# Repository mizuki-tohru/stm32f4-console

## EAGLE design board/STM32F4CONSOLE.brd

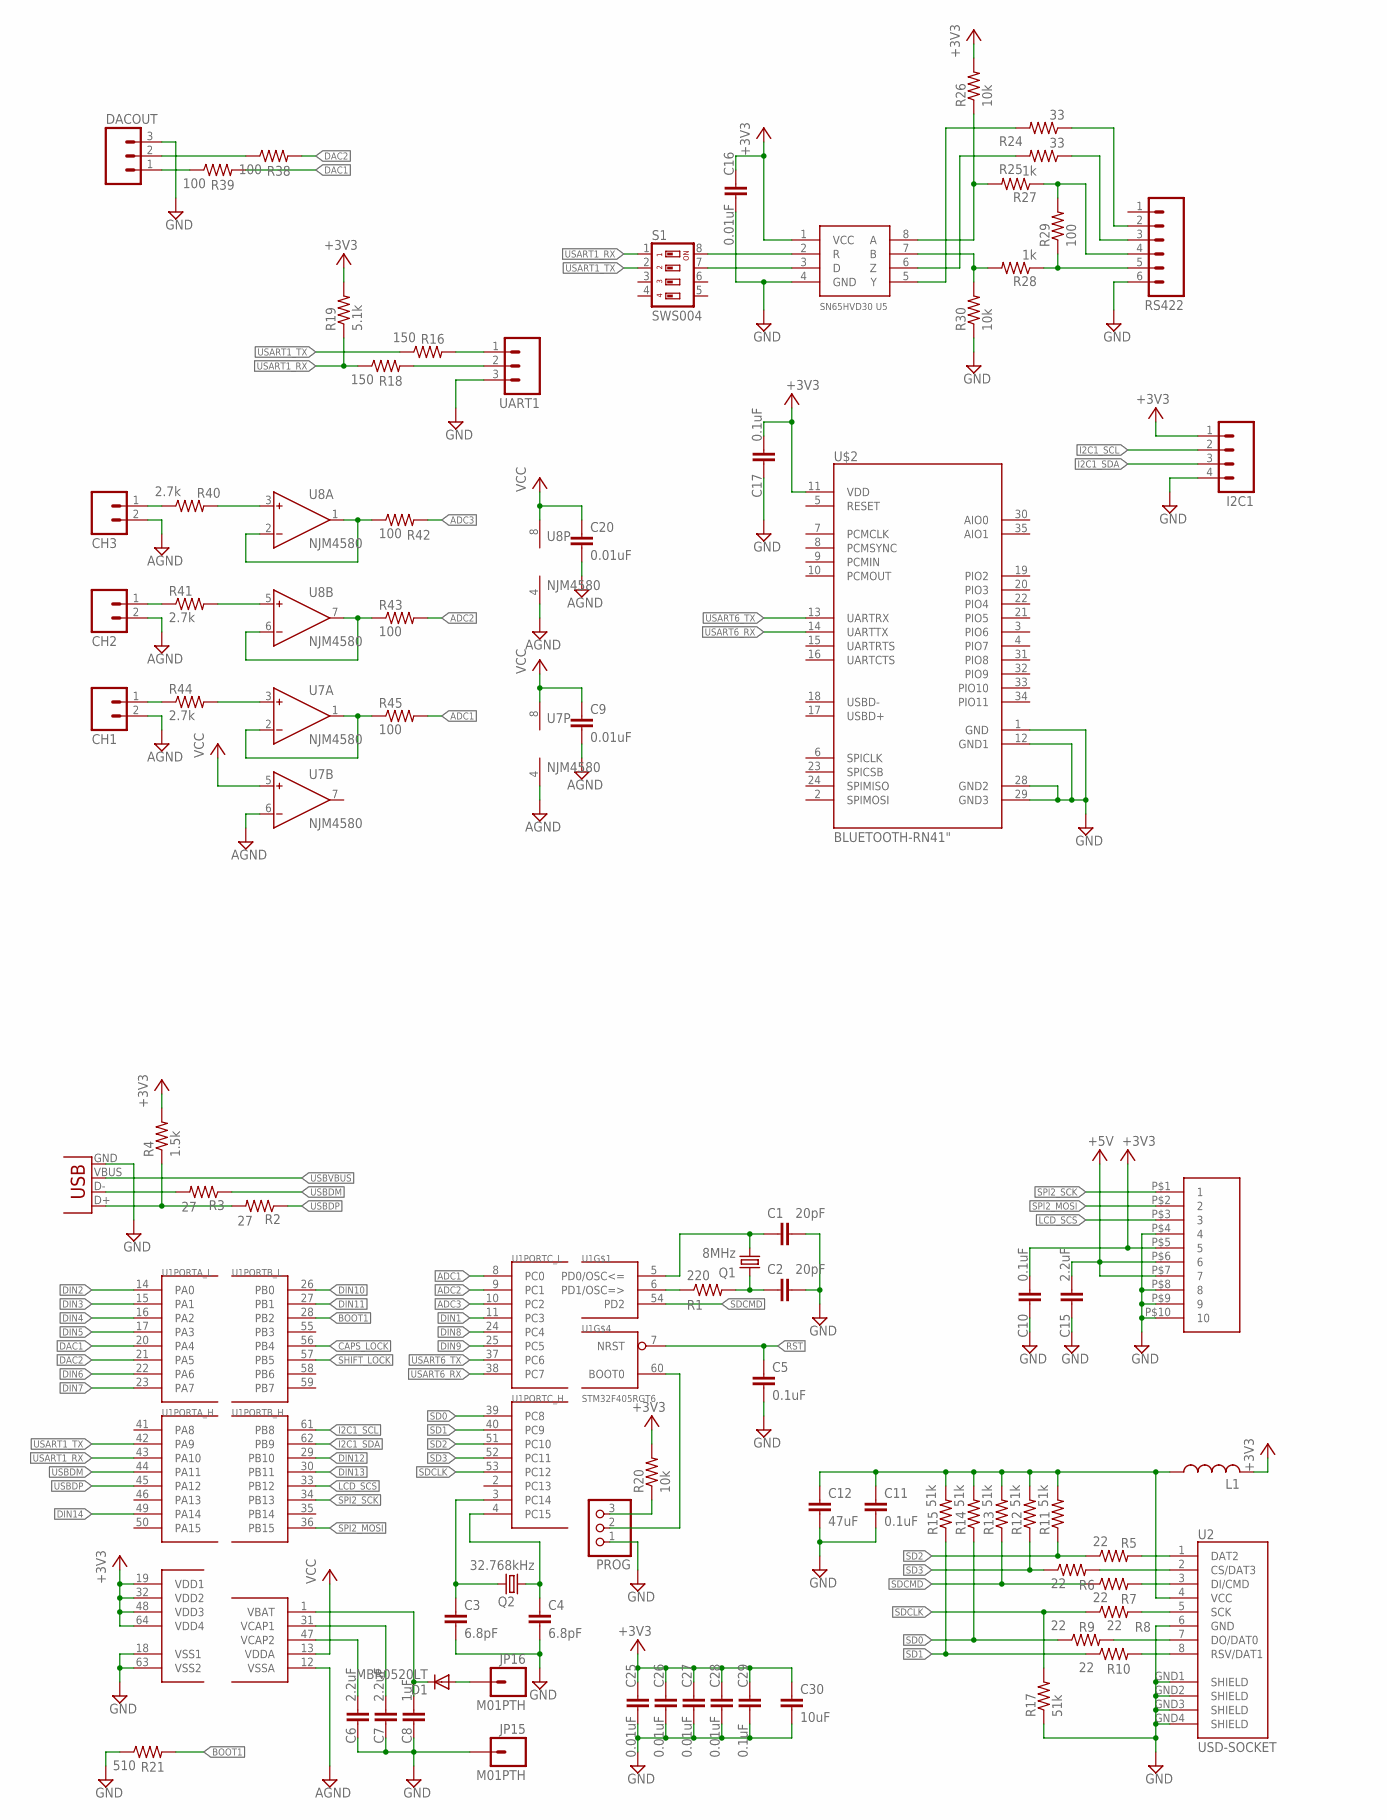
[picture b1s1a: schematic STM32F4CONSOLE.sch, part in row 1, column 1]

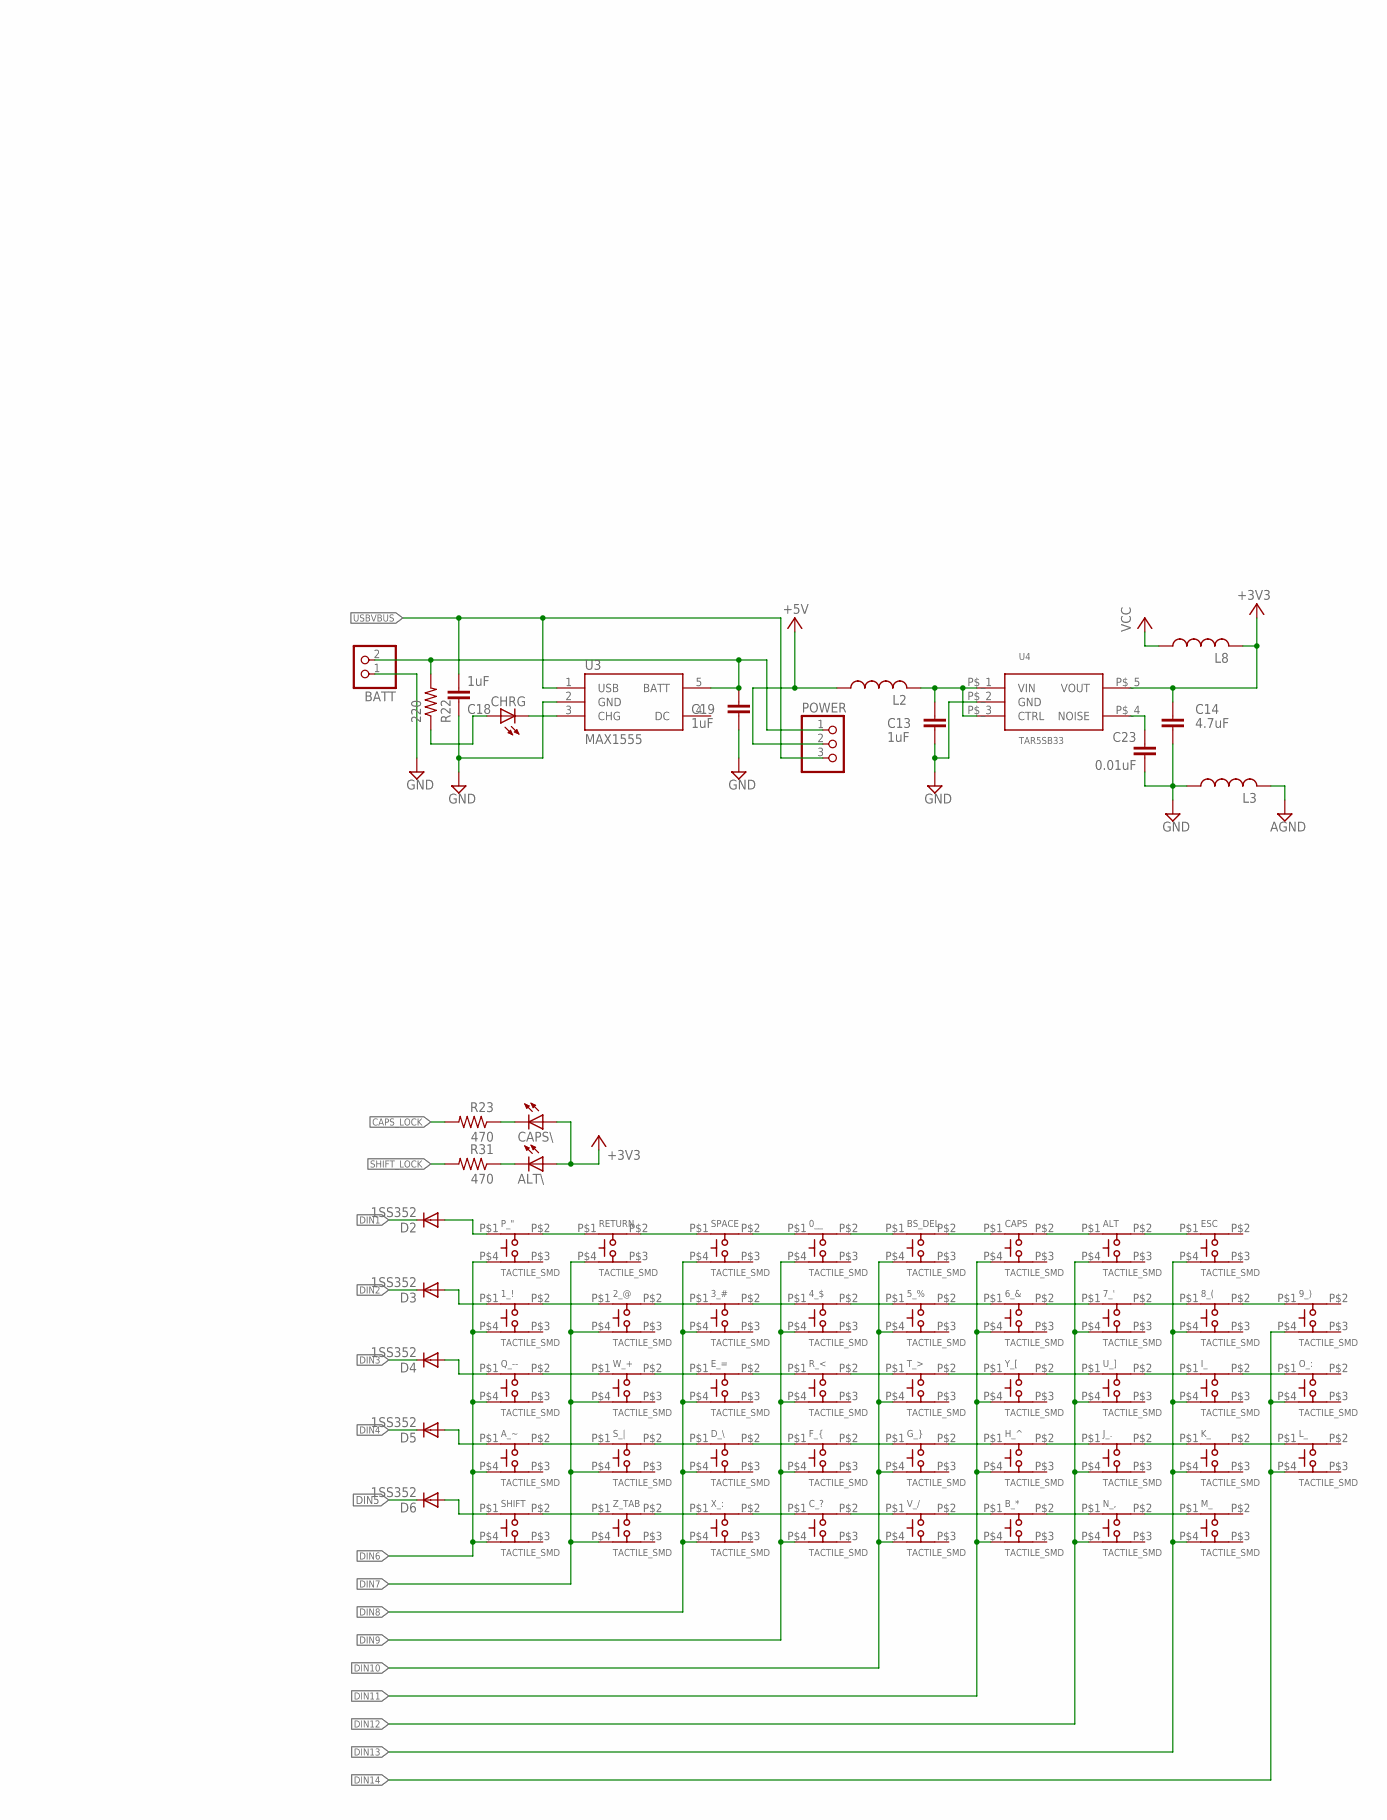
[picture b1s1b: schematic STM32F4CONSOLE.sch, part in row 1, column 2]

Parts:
0__, 1_!, 2_@, 3_#, 4_$, 5_%, 6_&, 7_', 8_(, 9_): TACTILE_SMD
ALT: TACTILE_SMD
ALT\: LED0603; LED-0603
A_~: TACTILE_SMD
BATT: PINHD-1X2; 1X02
BS_DEL: TACTILE_SMD
B_*: TACTILE_SMD
C1, C2: 20pF; C0603
C3, C4: 6.8pF; C0603
C5, C10, C11, C17, C29: 0.1uF; C0603
C6, C7, C15: 2.2uF; C0805
C8: 1uF; C1608
C9, C16, C20, C23, C25, C26, C27, C28: 0.01uF; C0603
C12: 47uF; C3225
C13, C18, C19: 1uF; C2012
C14: 4.7uF; C2012
C30: 10uF; C3216
CAPS: TACTILE_SMD
CAPS\: LED0603; LED-0603
CH1, CH2, CH3: M02PTH; 1X02
CHRG: LED0603; LED-0603
C_?: TACTILE_SMD
D1: MBR0520LT; SOD123
D2, D3, D4, D5, D6: 1SS352; SOD-323
DACOUT: M03PTH; 1X03
D_\\: TACTILE_SMD
ESC: TACTILE_SMD
E_=: TACTILE_SMD
F_{: TACTILE_SMD
G_}: TACTILE_SMD
H_^: TACTILE_SMD
I2C1: M04PTH; 1X04
I_: TACTILE_SMD
JP15, JP16: M01PTH; 1X01
J_.: TACTILE_SMD
K_: TACTILE_SMD
L1, L2, L3, L8: L-USL3216C; L3216C
L_: TACTILE_SMD
M_: TACTILE_SMD
N_,: TACTILE_SMD
O_:: TACTILE_SMD
POWER: PINHD-1X3; 1X03
PROG: PINHD-1X3; 1X03
P_": TACTILE_SMD
Q1: 8MHz; HC49/S
Q2: 32.768kHz; TC26H
Q_--: TACTILE_SMD
R1, R22: 220; R0603
R2, R3: 27; R0603
R4: 1.5k; R0603
R5, R6, R7, R8, R9, R10: 22; R0603
R11, R12, R13, R14, R15, R17: 51k; R0603
R16, R18: 150; R0603
R19: 5.1k; R0603
R20, R26, R30: 10k; R0603
R21: 510; R0603
R23, R31: 470; R0603
R24, R25: 33; R0603
R27, R28: 1k; R0603
R29, R38, R39, R42, R43, R45: 100; R0603
R40, R41, R44: 2.7k; R0805
RETURN: TACTILE_SMD
RS422: M06SIP; 1X06
R_<: TACTILE_SMD
S1: SWS004; SMSS-004
SHIFT: TACTILE_SMD
SPACE: TACTILE_SMD
S_|: TACTILE_SMD
T_>: TACTILE_SMD
U1: STM32F405RGT6; TQFP64
U2: USD-SOCKET; MICRO-SD-SOCKET-PP
U3: MAX1555; SOT23-5
U4: TAR5SB33
U5: SN65HVD30; SO8
U6: FH12-10S-05; FH12-10S-0.5SH
U7, U8: NJM4580; SO08
U$2: BLUETOOTH-RN41"; RN41
UART1: M03PTH; 1X03
U_]: TACTILE_SMD
V_/: TACTILE_SMD
W_+: TACTILE_SMD
X1: USBOLD; USB-MINIB-OLD
X_:: TACTILE_SMD
Y_[: TACTILE_SMD
Z_TAB: TACTILE_SMD

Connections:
+3V3: ALT\.A, C10.1, C14.1, C16.1, C17.1, C25.1, C26.1, C27.1, C28.1, C29.1, C30.1, CAPS\.A, I2C1.1, L1.2, L8.2, R4.2, R19.2, R20.2, R26.2, U1.19 (VDD1), U1.32 (VDD2), U1.48 (VDD3), U1.64 (VDD4), U4.P$_5 (VOUT), U5.1 (VCC), U6.P$5 (5), U$2.11 (VDD)
+5V: C15.1, L2.1, POWER.2, U6.P$6 (6), U6.P$7 (7)
ADC1: R45.2, U1.8 (PC0)
ADC2: R43.2, U1.9 (PC1)
ADC3: R42.2, U1.10 (PC2)
AGND: C9.2, C20.2, CH1.2, CH2.2, CH3.2, L3.2, U1.12 (VSSA), U7.4 (V-), U7.6 (IN-), U8.4 (V-)
BOOT1: R21.2, U1.28 (PB2)
CAPS_LOCK: R23.2, U1.56 (PB4)
DAC1: R39.2, U1.20 (PA4)
DAC2: R38.2, U1.21 (PA5)
DIN1: D2.1 (C), U1.11 (PC3)
DIN2: D3.1 (C), U1.14 (PA0)
DIN3: D4.1 (C), U1.15 (PA1)
DIN4: D5.1 (C), U1.16 (PA2)
DIN5: D6.1 (C), U1.17 (PA3)
DIN6: 1_!.P$4, A_~.P$4, P_".P$4, Q_--.P$4, SHIFT.P$4, U1.22 (PA6)
DIN7: 2_@.P$4, RETURN.P$4, S_|.P$4, U1.23 (PA7), W_+.P$4, Z_TAB.P$4
DIN8: 3_#.P$4, D_\\.P$4, E_=.P$4, SPACE.P$4, U1.24 (PC4), X_:.P$4
DIN9: 0__.P$4, 4_$.P$4, C_?.P$4, F_{.P$4, R_<.P$4, U1.25 (PC5)
DIN10: 5_%.P$4, BS_DEL.P$4, G_}.P$4, T_>.P$4, U1.26 (PB0), V_/.P$4
DIN11: 6_&.P$4, B_*.P$4, CAPS.P$4, H_^.P$4, U1.27 (PB1), Y_[.P$4
DIN12: 7_'.P$4, ALT.P$4, J_..P$4, N_,.P$4, U1.29 (PB10), U_].P$4
DIN13: 8_(.P$4, ESC.P$4, I_.P$4, K_.P$4, M_.P$4, U1.30 (PB11)
DIN14: 9_).P$4, L_.P$4, O_:.P$4, U1.49 (PA14)
DIN_2: 6_&.P$2, 7_'.P$1
DIN_3: I_.P$2, O_:.P$1
DIN_4: J_..P$2, K_.P$1
DIN_5: B_*.P$2, N_,.P$1
GND: BATT.1, C1.2, C2.2, C3.2, C4.2, C5.2, C6.2, C7.2, C8.2, C10.2, C11.2, C12.2, C13.2, C14.2, C15.2, C16.2, C17.2, C18.2, C19.2, C23.2, C25.2, C26.2, C27.2, C28.2, C29.2, C30.2, DACOUT.3, I2C1.4, JP15.1, L3.1, PROG.1, R17.1, R21.1, R30.1, RS422.6, U1.18 (VSS1), U1.63 (VSS2), U2.6 (GND), U2.GND1 (SHIELD), U2.GND2 (SHIELD), U2.GND3 (SHIELD), U2.GND4 (SHIELD), U3.2 (GND), U4.P$_2 (GND), U5.4 (GND), U6.P$4 (4), U6.P$8 (8), U6.P$9 (9), U6.P$10 (10), U$2.1 (GND), U$2.12 (GND1), U$2.28 (GND2), U$2.29 (GND3), UART1.3, X1.GND
I2C1_SCL: I2C1.2, U1.61 (PB8)
I2C1_SDA: I2C1.3, U1.62 (PB9)
LCD_SCS: U1.33 (PB12), U6.P$3 (3)
unnamed: R1.1, U1.6 (PD1/OSC=>)
unnamed: C2.1, Q1.1, R1.2
unnamed: C1.1, Q1.2, U1.5 (PD0/OSC<=)
unnamed: C6.1, U1.47 (VCAP2)
unnamed: C7.1, U1.31 (VCAP1)
unnamed: C4.1, Q2.2, U1.4 (PC15)
unnamed: C3.1, Q2.1, U1.3 (PC14)
unnamed: C8.1, D1.C, U1.1 (VBAT)
unnamed: R5.2, U2.1 (DAT2)
unnamed: R6.2, U2.2 (CS/DAT3)
unnamed: R7.2, U2.3 (DI/CMD)
unnamed: D1.A, JP16.1
unnamed: R8.2, U2.5 (SCK)
unnamed: R9.2, U2.7 (DO/DAT0)
unnamed: R10.2, U2.8 (RSV/DAT1)
unnamed: BATT.2, C19.1, POWER.1, R22.2, U3.5 (BATT)
unnamed: R3.2, X1.D-
unnamed: R2.2, R4.1, X1.D+
unnamed: R18.2, UART1.2
unnamed: R16.2, UART1.1
unnamed: PROG.2, U1.60 (BOOT0)
unnamed: C13.1, L2.2, U4.P$_1 (VIN), U4.P$_3 (CTRL)
unnamed: CHRG.A, R22.1
unnamed: CHRG.C, U3.3 (CHG)
unnamed: D2.2 (A), P_".P$1
unnamed: P_".P$2, RETURN.P$1
unnamed: RETURN.P$2, SPACE.P$1
unnamed: 0__.P$1, SPACE.P$2
unnamed: C11.1, C12.1, L1.1, R11.2, R12.2, R13.2, R14.2, R15.2, U2.4 (VCC)
unnamed: 0__.P$2, BS_DEL.P$1
unnamed: 1_!.P$1, D3.2 (A)
unnamed: 1_!.P$2, 2_@.P$1
unnamed: D6.2 (A), SHIFT.P$1
unnamed: SHIFT.P$2, Z_TAB.P$1
unnamed: C23.1, U4.P$_4 (NOISE)
unnamed: X_:.P$1, Z_TAB.P$2
unnamed: C_?.P$1, X_:.P$2
unnamed: C_?.P$2, V_/.P$1
unnamed: A_~.P$2, S_|.P$1
unnamed: F_{.P$2, G_}.P$1
unnamed: CH3.1, R40.1
unnamed: DACOUT.1, R39.1
unnamed: DACOUT.2, R38.1
unnamed: R40.2, U8.3 (IN+)
unnamed: CH2.1, R41.1
unnamed: R41.2, U8.5 (IN+)
unnamed: R43.1, U8.6 (IN-), U8.7 (OUT)
unnamed: R42.1, U8.1 (OUT), U8.2 (IN-)
unnamed: CH1.1, R44.1
unnamed: R44.2, U7.3 (IN+)
unnamed: R45.1, U7.1 (OUT), U7.2 (IN-)
unnamed: PROG.3, R20.1
unnamed: D_\\.P$2, F_{.P$1
unnamed: D_\\.P$1, S_|.P$2
unnamed: A_~.P$1, D5.2 (A)
unnamed: D4.2 (A), Q_--.P$1
unnamed: Q_--.P$2, W_+.P$1
unnamed: E_=.P$1, W_+.P$2
unnamed: E_=.P$2, R_<.P$1
unnamed: R_<.P$2, T_>.P$1
unnamed: 2_@.P$2, 3_#.P$1
unnamed: 3_#.P$2, 4_$.P$1
unnamed: 4_$.P$2, 5_%.P$1
unnamed: BS_DEL.P$2, CAPS.P$1
unnamed: ALT.P$1, CAPS.P$2
unnamed: ALT.P$2, ESC.P$1
unnamed: S1.7, U5.3 (D)
unnamed: S1.8, U5.2 (R)
unnamed: R24.2, U5.5 (Y)
unnamed: 8_(.P$2, 9_).P$1
unnamed: 7_'.P$2, 8_(.P$1
unnamed: 5_%.P$2, 6_&.P$1
unnamed: T_>.P$2, Y_[.P$1
unnamed: U_].P$1, Y_[.P$2
unnamed: I_.P$1, U_].P$2
unnamed: K_.P$2, L_.P$1
unnamed: R25.2, U5.6 (Z)
unnamed: M_.P$1, N_,.P$2
unnamed: B_*.P$1, V_/.P$2
unnamed: G_}.P$2, H_^.P$1
unnamed: H_^.P$2, J_..P$1
unnamed: R28.2, R30.2, U5.7 (B)
unnamed: R26.1, R27.2, U5.8 (A)
unnamed: R28.1, R29.1, RS422.5
unnamed: R27.1, R29.2, RS422.4
unnamed: R25.1, RS422.3
unnamed: R24.1, RS422.2
unnamed: CAPS\.C, R23.1
unnamed: ALT\.C, R31.1
RST: C5.1, U1.7 (NRST)
SD0: R9.1, R14.1, U1.39 (PC8)
SD1: R10.1, R15.1, U1.40 (PC9)
SD2: R5.1, R11.1, U1.51 (PC10)
SD3: R6.1, R12.1, U1.52 (PC11)
SDCLK: R8.1, R17.2, U1.53 (PC12)
SDCMD: R7.1, R13.1, U1.54 (PD2)
SHIFT_LOCK: R31.2, U1.57 (PB5)
SPI2_MOSI: U1.36 (PB15), U6.P$2 (2)
SPI2_SCK: U1.34 (PB13), U6.P$1 (1)
USART1_RX: R18.1, R19.1, S1.1, U1.43 (PA10)
USART1_TX: R16.1, S1.2, U1.42 (PA9)
USART6_RX: U1.38 (PC7), U$2.14 (UARTTX)
USART6_TX: U1.37 (PC6), U$2.13 (UARTRX)
USBDM: R3.1, U1.44 (PA11)
USBDP: R2.1, U1.45 (PA12)
USBVBUS: C18.1, POWER.3, U3.1 (USB), X1.VBUS
VCC: C9.1, C20.1, L8.1, U1.13 (VDDA), U7.5 (IN+), U7.8 (V+), U8.8 (V+)

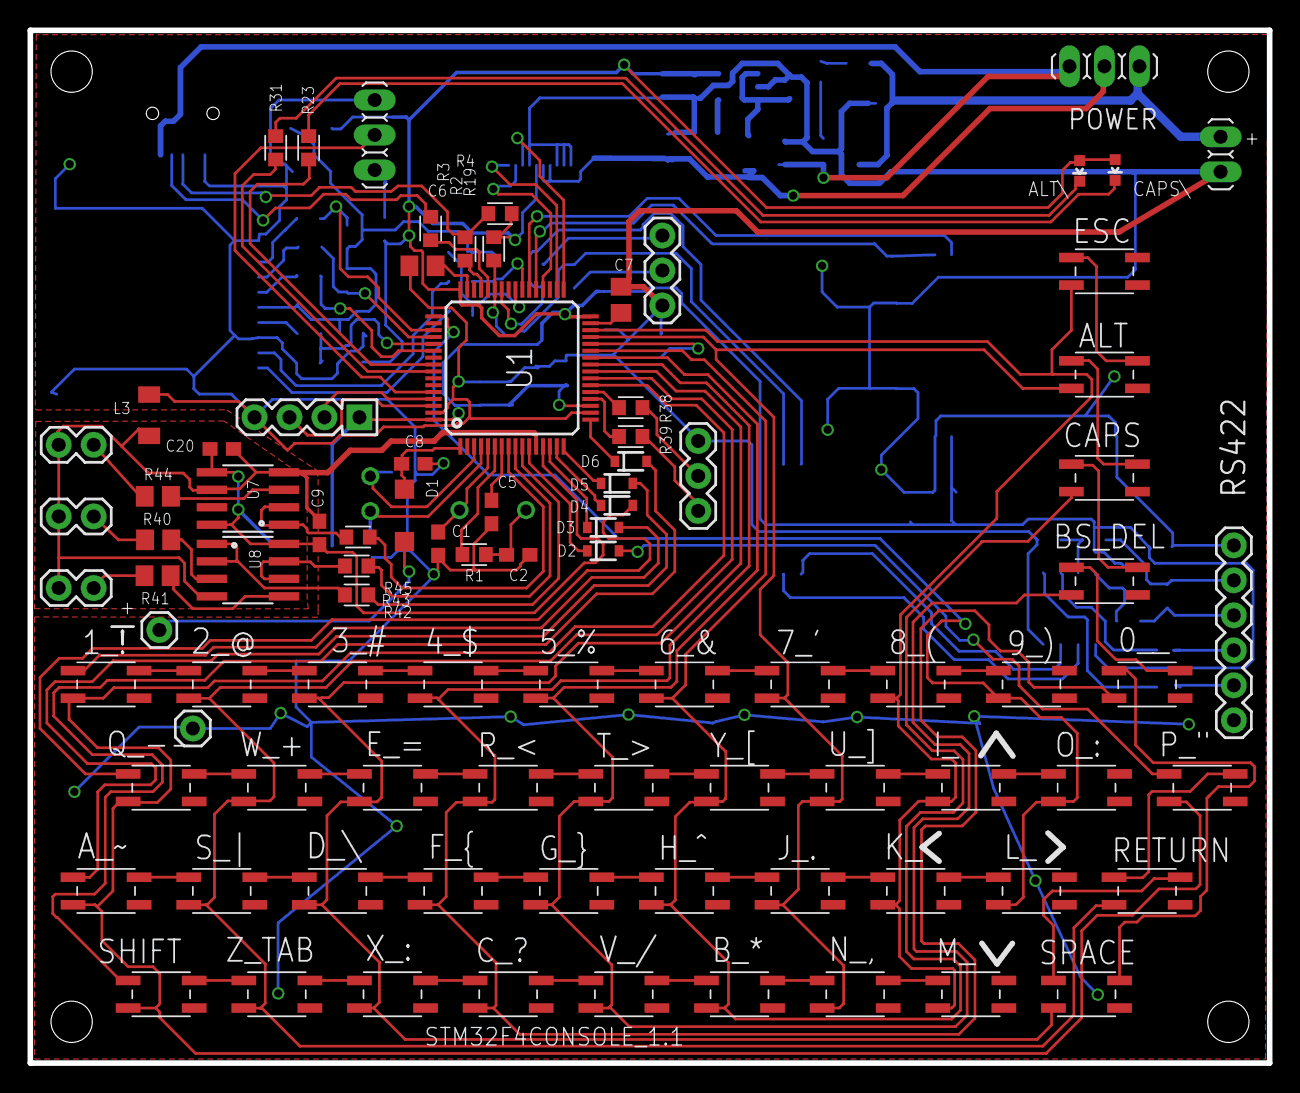
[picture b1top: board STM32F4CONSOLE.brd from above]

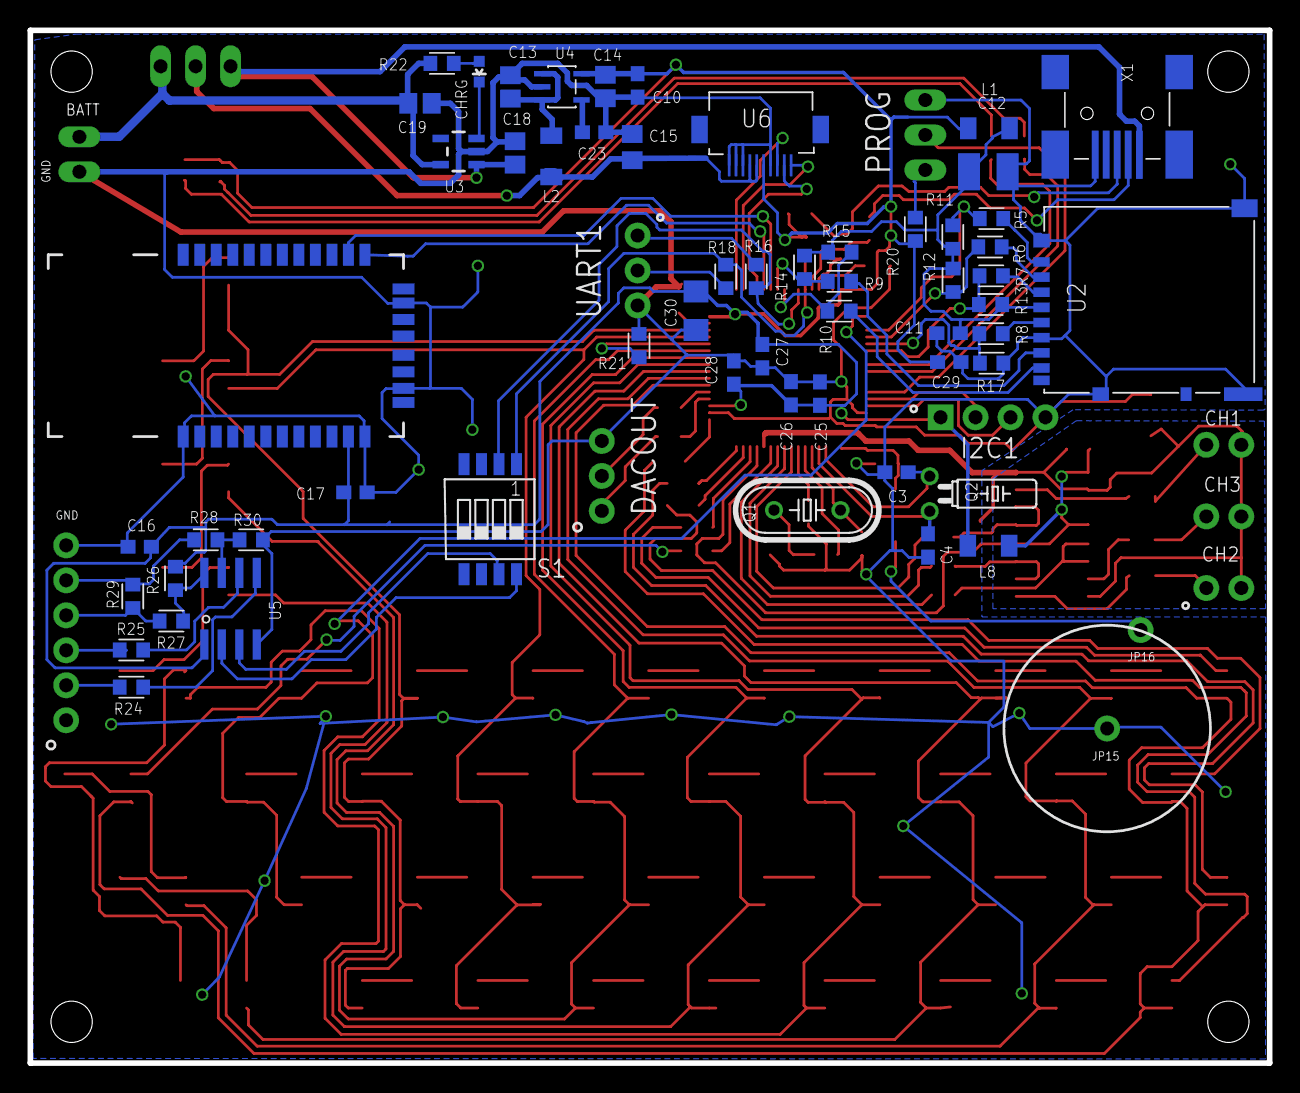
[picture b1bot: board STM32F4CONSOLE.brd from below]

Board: 2 copper layers, 90.0 x 75.0 mm, 147 parts (57 on the bottom side), 139 nets.

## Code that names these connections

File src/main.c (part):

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
uint8_t getData(void)
{
//	DIN1:PC3 DIN2:PA0 DIN3:PA1 DIN4:PA2
//	DIN5:PA3 DIN6:PA6 DIN7:PA7 DIN8:PC4

	uint8_t pa,pc,r;
	pa = GPIO_ReadInputData(GPIOA);
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}		

// ADC Init
// ADC1 :PC0/ADC123_IN10
// ADC2 :PC1/ADC123_IN11
// ADC3 :PC2/ADC123_IN12

void initADC()
{
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
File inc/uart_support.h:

/*
 UART2TX : PA2
 UART2RX : PA3
 UART3TX : PD8
 UART3RX : PD9
 UART4TX : PA0
 UART4RX : PA1
 UART6TX : PC6
 UART6RX : PC7
*/



#ifndef __UART_SUPPORT_H
#define __UART_SUPPORT_H

#ifdef __cplusplus
 extern "C" {
#endif

/* General Inclusion */
#include <stdio.h>
#include <stdlib.h>
#include <string.h>
#include <stdbool.h>
#include <inttypes.h>

/* uC Specific Inclusion */
#include "stm32f4xx.h"
#include "stm32f4xx_it.h"
#include "stm32f4xx_conf.h"

/* USART Definition */
#define UART_BUFSIZE		256
//#define UART_BAUDLATE		9600UL
//#define UART_BAUDLATE		115200UL
#define UART_BAUDLATE		38400UL
#define UART_DEFAULT_NUM	1 /*USART2 PA2,PA3 default use*/

/* General Definition */
#define countof(a)   (sizeof(a) / sizeof(*(a)))

/* Funcion Prototypes */
extern void conio_init(uint32_t port, uint32_t baudrate);
extern void set_defalt_cino_port(uint32_t port);
extern void putch(uint8_t c);
extern void putch_p(uint32_t port,uint8_t c);
extern uint8_t getch(void);
extern uint8_t getch_p(uint32_t port);
extern uint16_t getch_p16(uint32_t port);
extern uint8_t keypressed(uint32_t port);
extern void cputs(char *s);
extern void cputs_p(uint32_t, char *);
extern void cgets(uint32_t port,char *s, int bufsize);

/* Structs */
/* This is From AVRX uC Sample!!! */
/* @brief USART transmit and receive ring buffer. */
typedef struct USART_Buffer
{
	/* @brief Receive buffer. */
	volatile uint8_t RX[UART_BUFSIZE];
	/* @brief Transmit buffer. */
	volatile uint8_t TX[UART_BUFSIZE];
	/* @brief Receive buffer head. */
	volatile uint16_t RX_Head;
	/* @brief Receive buffer tail. */
	volatile uint16_t RX_Tail;
	/* @brief Transmit buffer head. */
	volatile uint16_t TX_Head;
	/* @brief Transmit buffer tail. */
	volatile uint16_t TX_Tail;
} USART_Buffer_t;

/* Externs */
extern USART_Buffer_t USART1_Buf;
extern USART_Buffer_t USART2_Buf;
extern USART_Buffer_t USART3_Buf;
extern USART_Buffer_t UART4_Buf;
extern USART_Buffer_t USART6_Buf;

#ifdef __cplusplus
}
#endif

#endif	/* __UART_SUPPORT_H */

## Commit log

2014-08-18 version C86

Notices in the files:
parts and their libraries:
SparkFun-RF: Licensing: CC v3.0 Share-Alike You are welcome to use this library for commercial purposes.
